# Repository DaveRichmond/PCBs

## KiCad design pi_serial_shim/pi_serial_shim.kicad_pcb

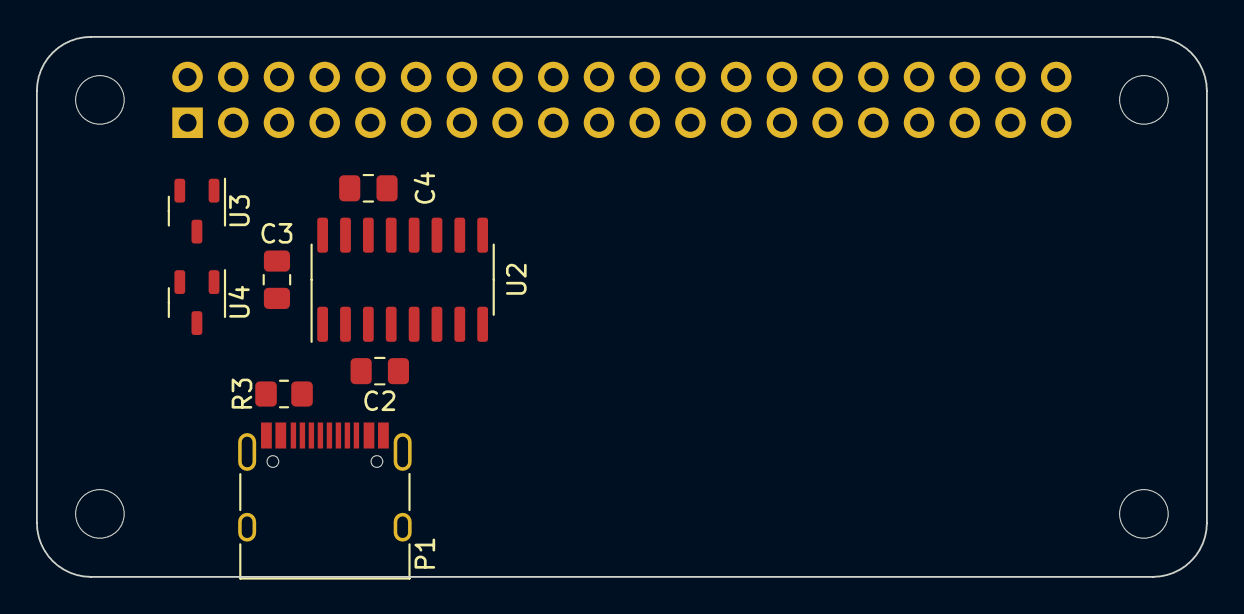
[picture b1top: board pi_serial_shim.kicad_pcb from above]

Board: 2 copper layers, 65.0 x 30.0 mm, 13 parts (1 on the bottom side), 10 nets, no tracks yet.

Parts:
C2: 100n; C_0805_2012Metric_Pad1.18x1.45mm_HandSolder
C3, C4: 1u; C_0805_2012Metric_Pad1.18x1.45mm_HandSolder
J1: GPIO; PinSocket_2x20_P2.54mm_Vertical
MH1, MH2, MH3, MH4: MountingHole_2.7mm_M2.5
P1: USB_C_Plug_USB2.0; USB_C_Receptacle_HRO_TYPE-C-31-M-12
R3: 56k; R_0805_2012Metric_Pad1.20x1.40mm_HandSolder
U2: SOIC-16_3.9x9.9mm_P1.27mm
U3, U4: SOT-23-3

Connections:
+3.3V: C4.1, J1.1, J1.17, U2.15 (VIO), U3.2 (VO)
+5V: C3.1, J1.2, J1.4, U2.16 (VCC), U4.2 (VO)
/GPIO14/TXD0: J1.8, U2.3 (RXD)
/GPIO15/RXD0: J1.10, U2.2 (TXD)
GND: C2.2, C3.2, C4.2, J1.6, J1.9, J1.14, J1.20, J1.25, J1.30, J1.34, J1.39, P1.A1 (GND), P1.A12 (GND), P1.B1 (GND), P1.B12 (GND), P1.S1 (SHIELD), U2.1 (GND), U3.1 (GND), U4.1 (GND)
unnamed: P1.A5 (CC), R3.2
unnamed: P1.A6 (D+), U2.5 (UD+)
unnamed: P1.A7 (D-), U2.6 (UD-)
unnamed: P1.A4 (VBUS), P1.A9 (VBUS), P1.B4 (VBUS), P1.B5 (VCONN), P1.B9 (VBUS), R3.1, U4.3 (VI)
unnamed: C2.1, U2.4 (V3), U3.3 (VI)

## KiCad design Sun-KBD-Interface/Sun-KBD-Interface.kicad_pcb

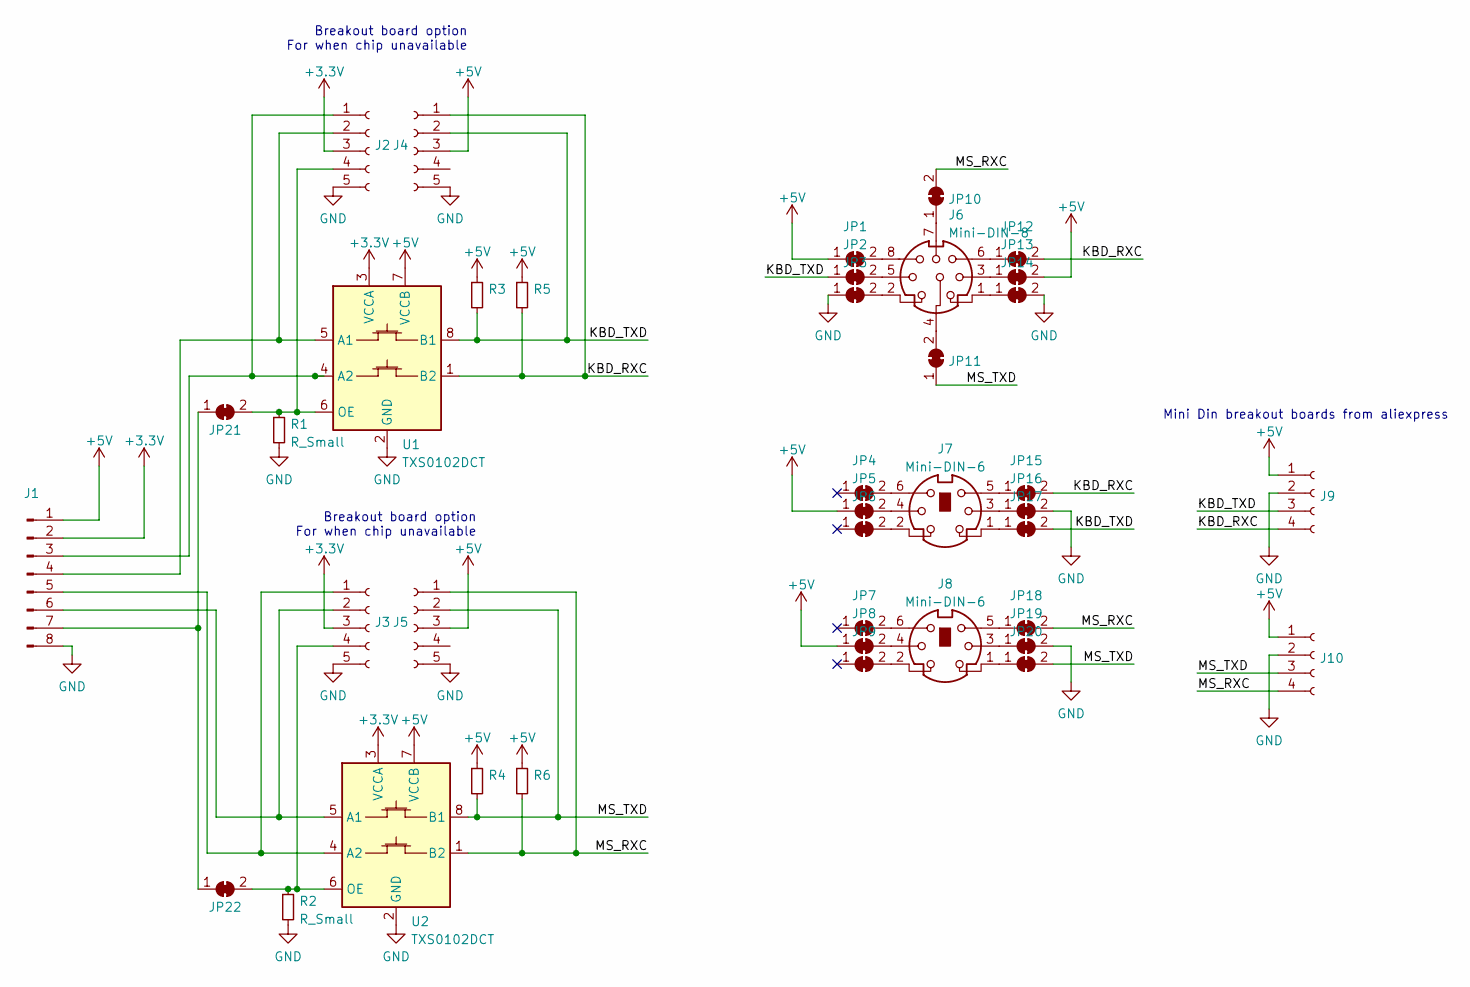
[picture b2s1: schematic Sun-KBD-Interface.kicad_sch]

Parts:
J1: Conn_01x08_Male; PinHeader_1x08_P2.54mm_Vertical
J2, J3, J4, J5: Conn_01x05_Female; PinHeader_1x05_P2.54mm_Vertical
J6: Mini-DIN-8; Mini-DIN 8
J7, J8: Mini-DIN-6; Mini-DIN 6
J9, J10: Conn_01x04_Female; PinSocket_1x04_P2.54mm_Vertical
JP1, JP2, JP3, JP4, JP5, JP6, JP7, JP8, JP9, JP10, JP11, JP12, JP13, JP14, JP15, JP16, JP17, JP18, JP19, JP20, JP21, JP22: SolderJumper_2_Bridged; SolderJumper-2_P1.3mm_Bridged_RoundedPad1.0x1.5mm
R1, R2, R3, R4, R5, R6: R_Small; R_1206_3216Metric_Pad1.30x1.75mm_HandSolder
U1, U2: TXS0102DCT; SSOP-8_2.95x2.8mm_P0.65mm

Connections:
+3.3V: J1.2, J2.3, J3.3, U1.3 (VCCA), U2.3 (VCCA)
+5V: J1.1, J4.3, J5.3, J9.1, J10.1, JP1.1 (A), JP5.1 (A), JP8.1 (A), JP13.2 (B), R3.1, R4.1, R5.1, R6.1, U1.7 (VCCB), U2.7 (VCCB)
/KBD_RXC: J4.1, J9.4, JP12.2 (B), JP15.2 (B), R5.2, U1.1 (B2)
/KBD_TXD: J4.2, J9.3, JP2.1 (A), JP17.2 (B), R3.2, U1.8 (B1)
/MS_RXC: J5.1, J10.4, JP10.2 (B), JP18.2 (B), R6.2, U2.1 (B2)
/MS_TXD: J5.2, J10.3, JP11.1 (A), JP20.2 (B), R4.2, U2.8 (B1)
GND: J1.8, J2.5, J3.5, J4.5, J5.5, J9.2, J10.2, JP3.1 (A), JP14.2 (B), JP16.2 (B), JP19.2 (B), R1.2, R2.2, U1.2 (GND), U2.2 (GND)
unnamed: J1.3, J2.1, U1.4 (A2)
unnamed: J1.4, J2.2, U1.5 (A1)
unnamed: J1.5, J3.1, U2.4 (A2)
unnamed: J1.6, J3.2, U2.5 (A1)
unnamed: J1.7, JP21.1 (A), JP22.1 (A)
unnamed: J2.4, JP21.2 (B), R1.1, U1.6 (OE)
unnamed: J3.4, JP22.2 (B), R2.1, U2.6 (OE)
unnamed: J6.1, JP14.1 (A)
unnamed: J6.2, JP3.2 (B)
unnamed: J6.3, JP13.1 (A)
unnamed: J6.4, JP11.2 (B)
unnamed: J6.5, JP2.2 (B)
unnamed: J6.6, JP12.1 (A)
unnamed: J6.7, JP10.1 (A)
unnamed: J6.8, JP1.2 (B)
unnamed: J7.1, JP17.1 (A)
unnamed: J7.2, JP6.2 (B)
unnamed: J7.3, JP16.1 (A)
unnamed: J7.4, JP5.2 (B)
unnamed: J7.5, JP15.1 (A)
unnamed: J7.6, JP4.2 (B)
unnamed: J8.1, JP20.1 (A)
unnamed: J8.2, JP9.2 (B)
unnamed: J8.3, JP19.1 (A)
unnamed: J8.4, JP8.2 (B)
unnamed: J8.5, JP18.1 (A)
unnamed: J8.6, JP7.2 (B)

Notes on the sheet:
Breakout board option For when chip unavailable
Mini Din breakout boards from aliexpress

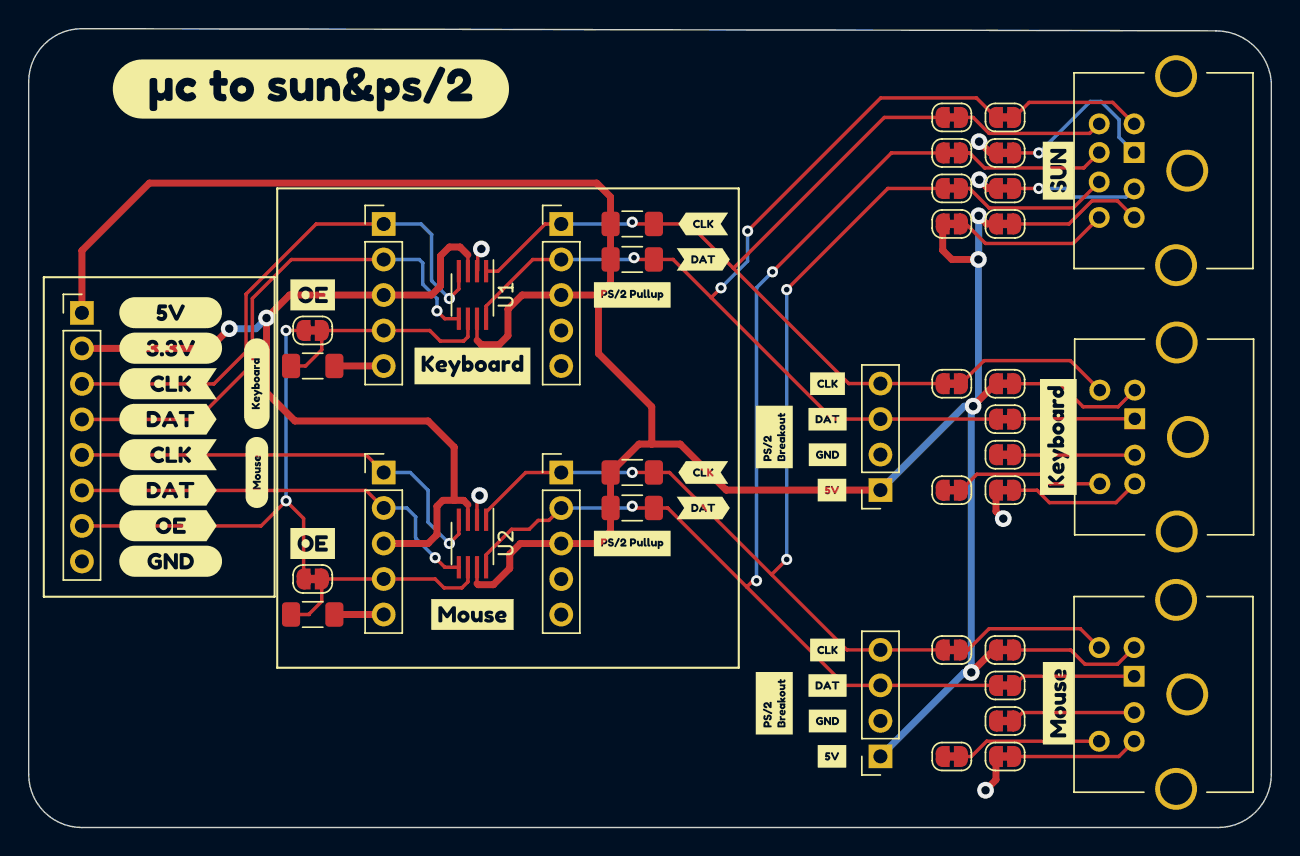
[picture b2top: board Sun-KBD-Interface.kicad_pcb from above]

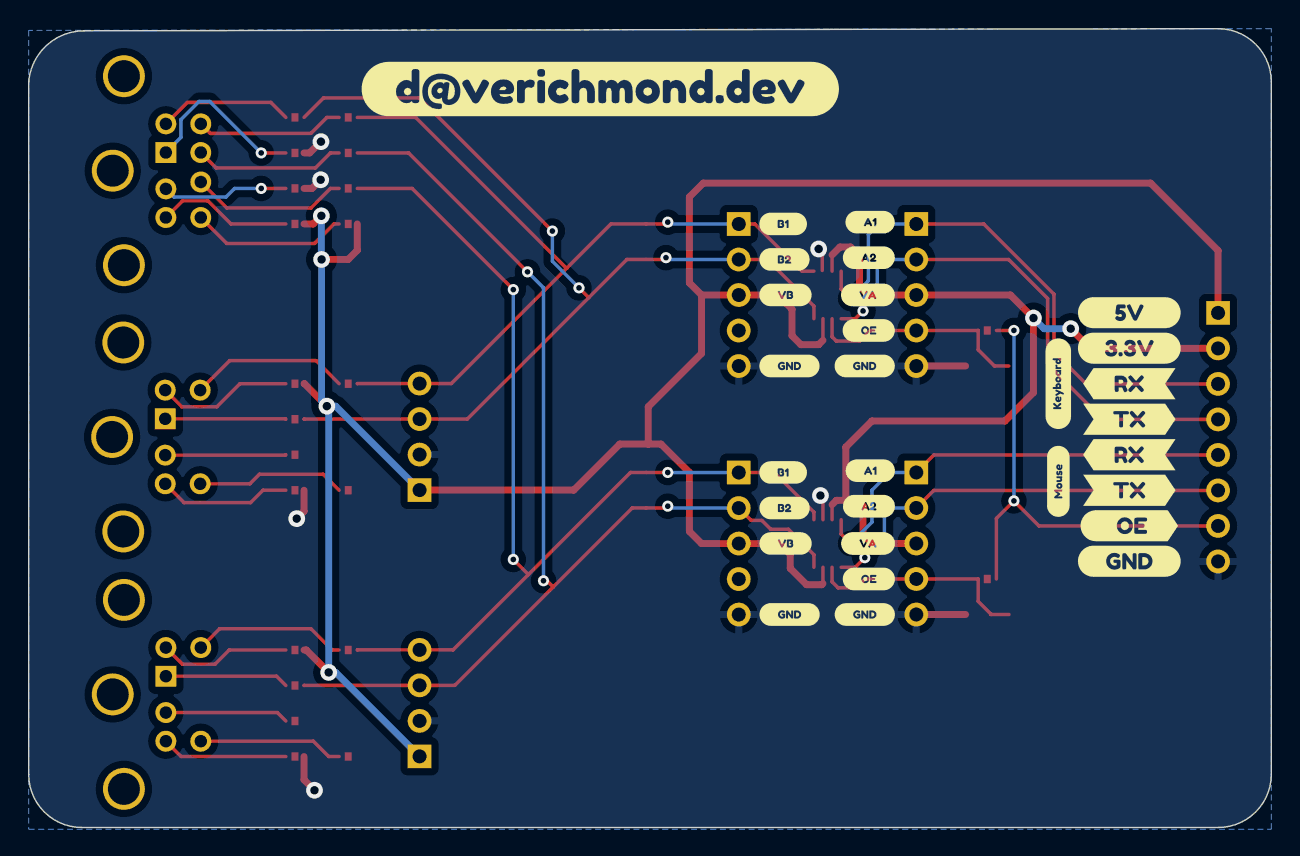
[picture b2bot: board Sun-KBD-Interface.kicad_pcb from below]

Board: 2 copper layers, 88.9 x 57.1 mm, 103 parts (29 on the bottom side), 34 nets.

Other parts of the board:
kibuzzard-1: G***; kibuzzard-6300B3A5
kibuzzard-2: G***; kibuzzard-6300B393
kibuzzard-3, kibuzzard-32: G***; kibuzzard-6300B04A
kibuzzard-4, kibuzzard-17: G***; kibuzzard-6300AFFB
kibuzzard-5, kibuzzard-19: G***; kibuzzard-6300B08C
kibuzzard-6, kibuzzard-21: G***; kibuzzard-6300B0E5
kibuzzard-7, kibuzzard-20: G***; kibuzzard-6300B0D2
kibuzzard-8: G***; kibuzzard-6300B1CF
kibuzzard-9, kibuzzard-9#2: G***; kibuzzard-6300B31A
kibuzzard-10, kibuzzard-12: G***; kibuzzard-6300B379
kibuzzard-11, kibuzzard-14: G***; kibuzzard-6300B34C
kibuzzard-13, kibuzzard-13#2: G***; kibuzzard-6300B361
kibuzzard-15, kibuzzard-15#2: G***; kibuzzard-6300B3DE
kibuzzard-16, kibuzzard-31: G***; kibuzzard-6300B05D
kibuzzard-18, kibuzzard-18#2: G***; kibuzzard-6300B3ED
kibuzzard-22, kibuzzard-23: G***; kibuzzard-6300B12D
kibuzzard-24, kibuzzard-29: G***; kibuzzard-6300B164
kibuzzard-25, kibuzzard-27: G***; kibuzzard-6300B180
kibuzzard-26, kibuzzard-28: G***; kibuzzard-6300B189
kibuzzard-30, kibuzzard-33: G***; kibuzzard-6300B14F
kibuzzard-63B4EFA4: G***; kibuzzard-63B4EFA4
kibuzzard-63B4EFB4: G***; kibuzzard-63B4EFB4
kibuzzard-63B4F027, kibuzzard-63B4F027#2: G***; kibuzzard-63B4F027
kibuzzard-63B4F037, kibuzzard-63B4F037#2: G***; kibuzzard-63B4F037
kibuzzard-63043A3B, kibuzzard-63043A3B#2: G***; kibuzzard-63043A3B
kibuzzard-63043A22, kibuzzard-63043A22#2: G***; kibuzzard-63043A22
kibuzzard-63043A32, kibuzzard-63043A32#2: G***; kibuzzard-63043A32
kibuzzard-63043B6D: G***; kibuzzard-63043B6D
kibuzzard-63043B8B: G***; kibuzzard-63043B8B
kibuzzard-630439AA, kibuzzard-630439AA#2: G***; kibuzzard-630439AA
kibuzzard-630439CC, kibuzzard-630439CC#2: G***; kibuzzard-630439CC
kibuzzard-630439D9, kibuzzard-630439D9#2: G***; kibuzzard-630439D9
kibuzzard-630439E7, kibuzzard-630439E7#2: G***; kibuzzard-630439E7
kibuzzard-630439F1, kibuzzard-630439F1#2, kibuzzard-630439F1#3, kibuzzard-630439F1#4: G***; kibuzzard-630439F1

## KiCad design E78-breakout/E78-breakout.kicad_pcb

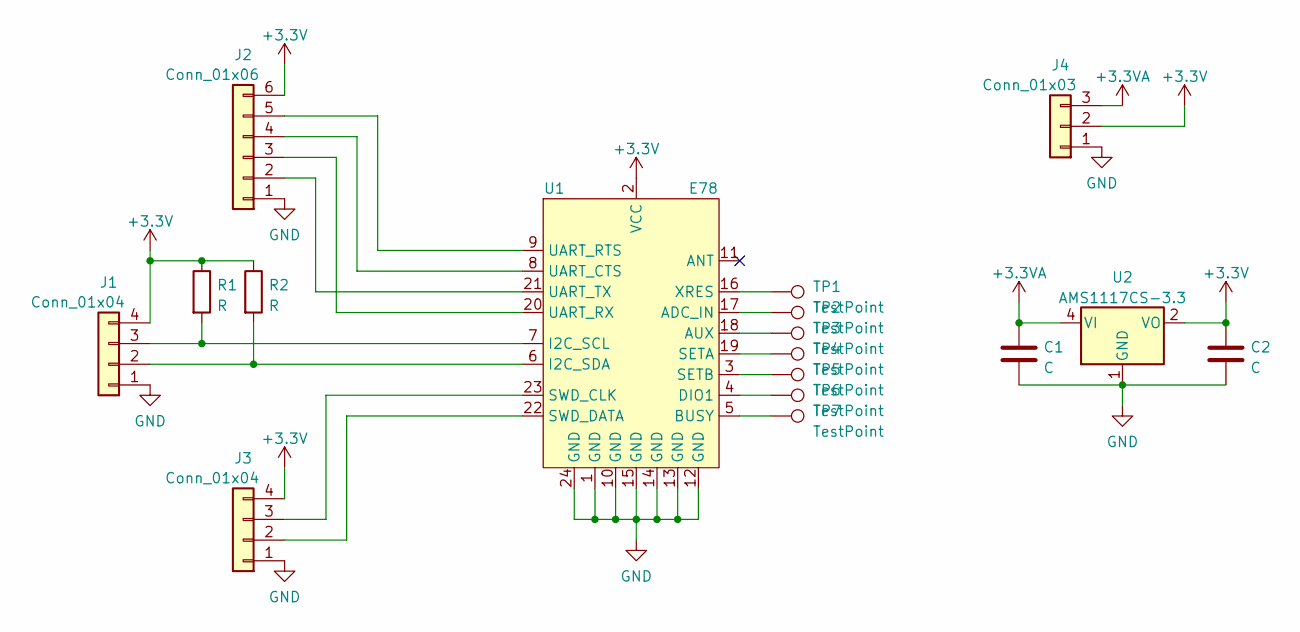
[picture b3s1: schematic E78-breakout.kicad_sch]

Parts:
C1, C2: C; C_0805_2012Metric_Pad1.18x1.45mm_HandSolder
J1, J3: Conn_01x04; PinSocket_1x04_P2.54mm_Vertical
J2: Conn_01x06; PinSocket_1x06_P2.54mm_Vertical
J4: Conn_01x03; PinSocket_1x03_P2.54mm_Vertical
R1, R2: R; R_0805_2012Metric_Pad1.20x1.40mm_HandSolder
TP1, TP2, TP3, TP4, TP5, TP6, TP7: TestPoint; TestPoint_Pad_D1.5mm
U1: E78; ebyte e78
U2: AMS1117CS-3.3; SOIC-8_3.9x4.9mm_P1.27mm

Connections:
+3.3VA: C1.1, J4.3, U2.4 (VI)
+3V3: C2.1, J1.4, J2.6, J3.4, J4.2, R1.1, R2.1, U1.2 (VCC), U2.2 (VO), U2.3 (VO), U2.6 (VO), U2.7 (VO)
GND: C1.2, C2.2, J1.1, J2.1, J3.1, J4.1, U1.1 (GND), U1.10 (GND), U1.12 (GND), U1.13 (GND), U1.14 (GND), U1.15 (GND), U1.24 (GND), U2.1 (GND)
unnamed: J1.2, R2.2, U1.6 (I2C_SDA)
unnamed: J1.3, R1.2, U1.7 (I2C_SCL)
unnamed: J2.2, U1.21 (UART_TX)
unnamed: J2.3, U1.20 (UART_RX)
unnamed: J2.4, U1.8 (UART_CTS)
unnamed: J2.5, U1.9 (UART_RTS)
unnamed: J3.2, U1.22 (SWD_DATA)
unnamed: J3.3, U1.23 (SWD_CLK)
unnamed: TP2.1, U1.17 (ADC_IN)
unnamed: TP3.1, U1.18 (AUX)
unnamed: TP7.1, U1.5 (BUSY)
unnamed: TP6.1, U1.4 (DIO1)
unnamed: TP4.1, U1.19 (SETA)
unnamed: TP5.1, U1.3 (SETB)
unnamed: TP1.1, U1.16 (XRES)

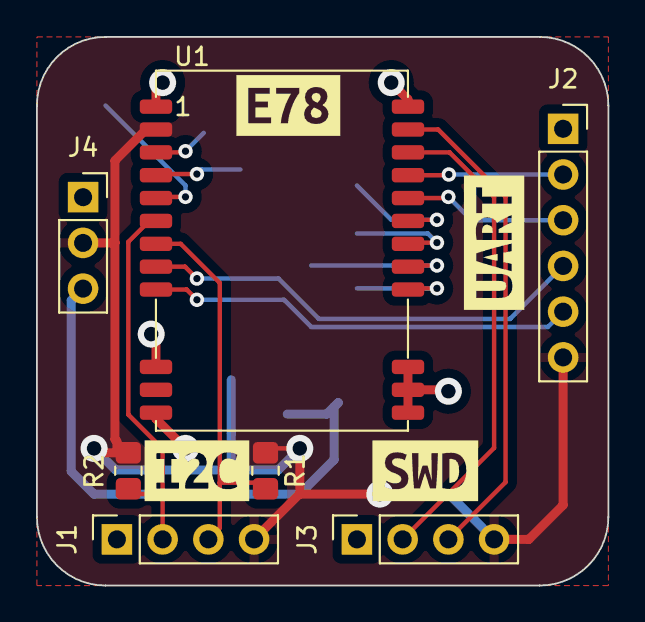
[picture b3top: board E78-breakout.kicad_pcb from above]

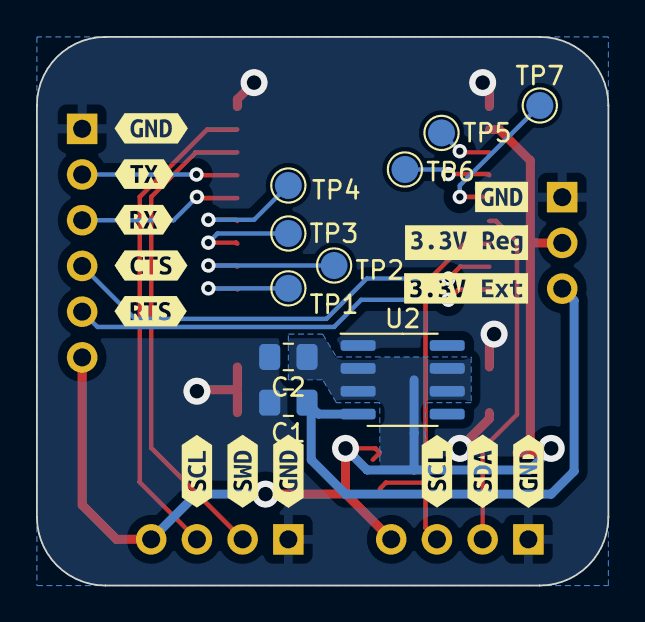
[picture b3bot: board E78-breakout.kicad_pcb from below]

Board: 2 copper layers, 31.8 x 30.5 mm, 35 parts (24 on the bottom side), 18 nets.

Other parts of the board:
kibuzzard-64A3B5A1: G***; kibuzzard-64A3B5A1
kibuzzard-64A3B5B5: G***; kibuzzard-64A3B5B5
kibuzzard-64A3B5D3: G***; kibuzzard-64A3B5D3
kibuzzard-64A3B52E: G***; kibuzzard-64A3B52E
kibuzzard-64A3B61D: G***; kibuzzard-64A3B61D
kibuzzard-64A3B63B: G***; kibuzzard-64A3B63B
kibuzzard-64A3B516: G***; kibuzzard-64A3B516
kibuzzard-64A3B571: G***; kibuzzard-64A3B571
kibuzzard-64A3B602: G***; kibuzzard-64A3B602
kibuzzard-64A3B618: G***; kibuzzard-64A3B618
kibuzzard-64A3B637: G***; kibuzzard-64A3B637
kibuzzard-6402D7DF: G***; kibuzzard-6402D7DF
kibuzzard-6402D81D: G***; kibuzzard-6402D81D
kibuzzard-6402D83E: G***; kibuzzard-6402D83E
kibuzzard-6402D86B: G***; kibuzzard-6402D86B
kibuzzard-6402D830: G***; kibuzzard-6402D830
kibuzzard-6402D864: G***; kibuzzard-6402D864
kibuzzard-6402EA7B: G***; kibuzzard-6402EA7B

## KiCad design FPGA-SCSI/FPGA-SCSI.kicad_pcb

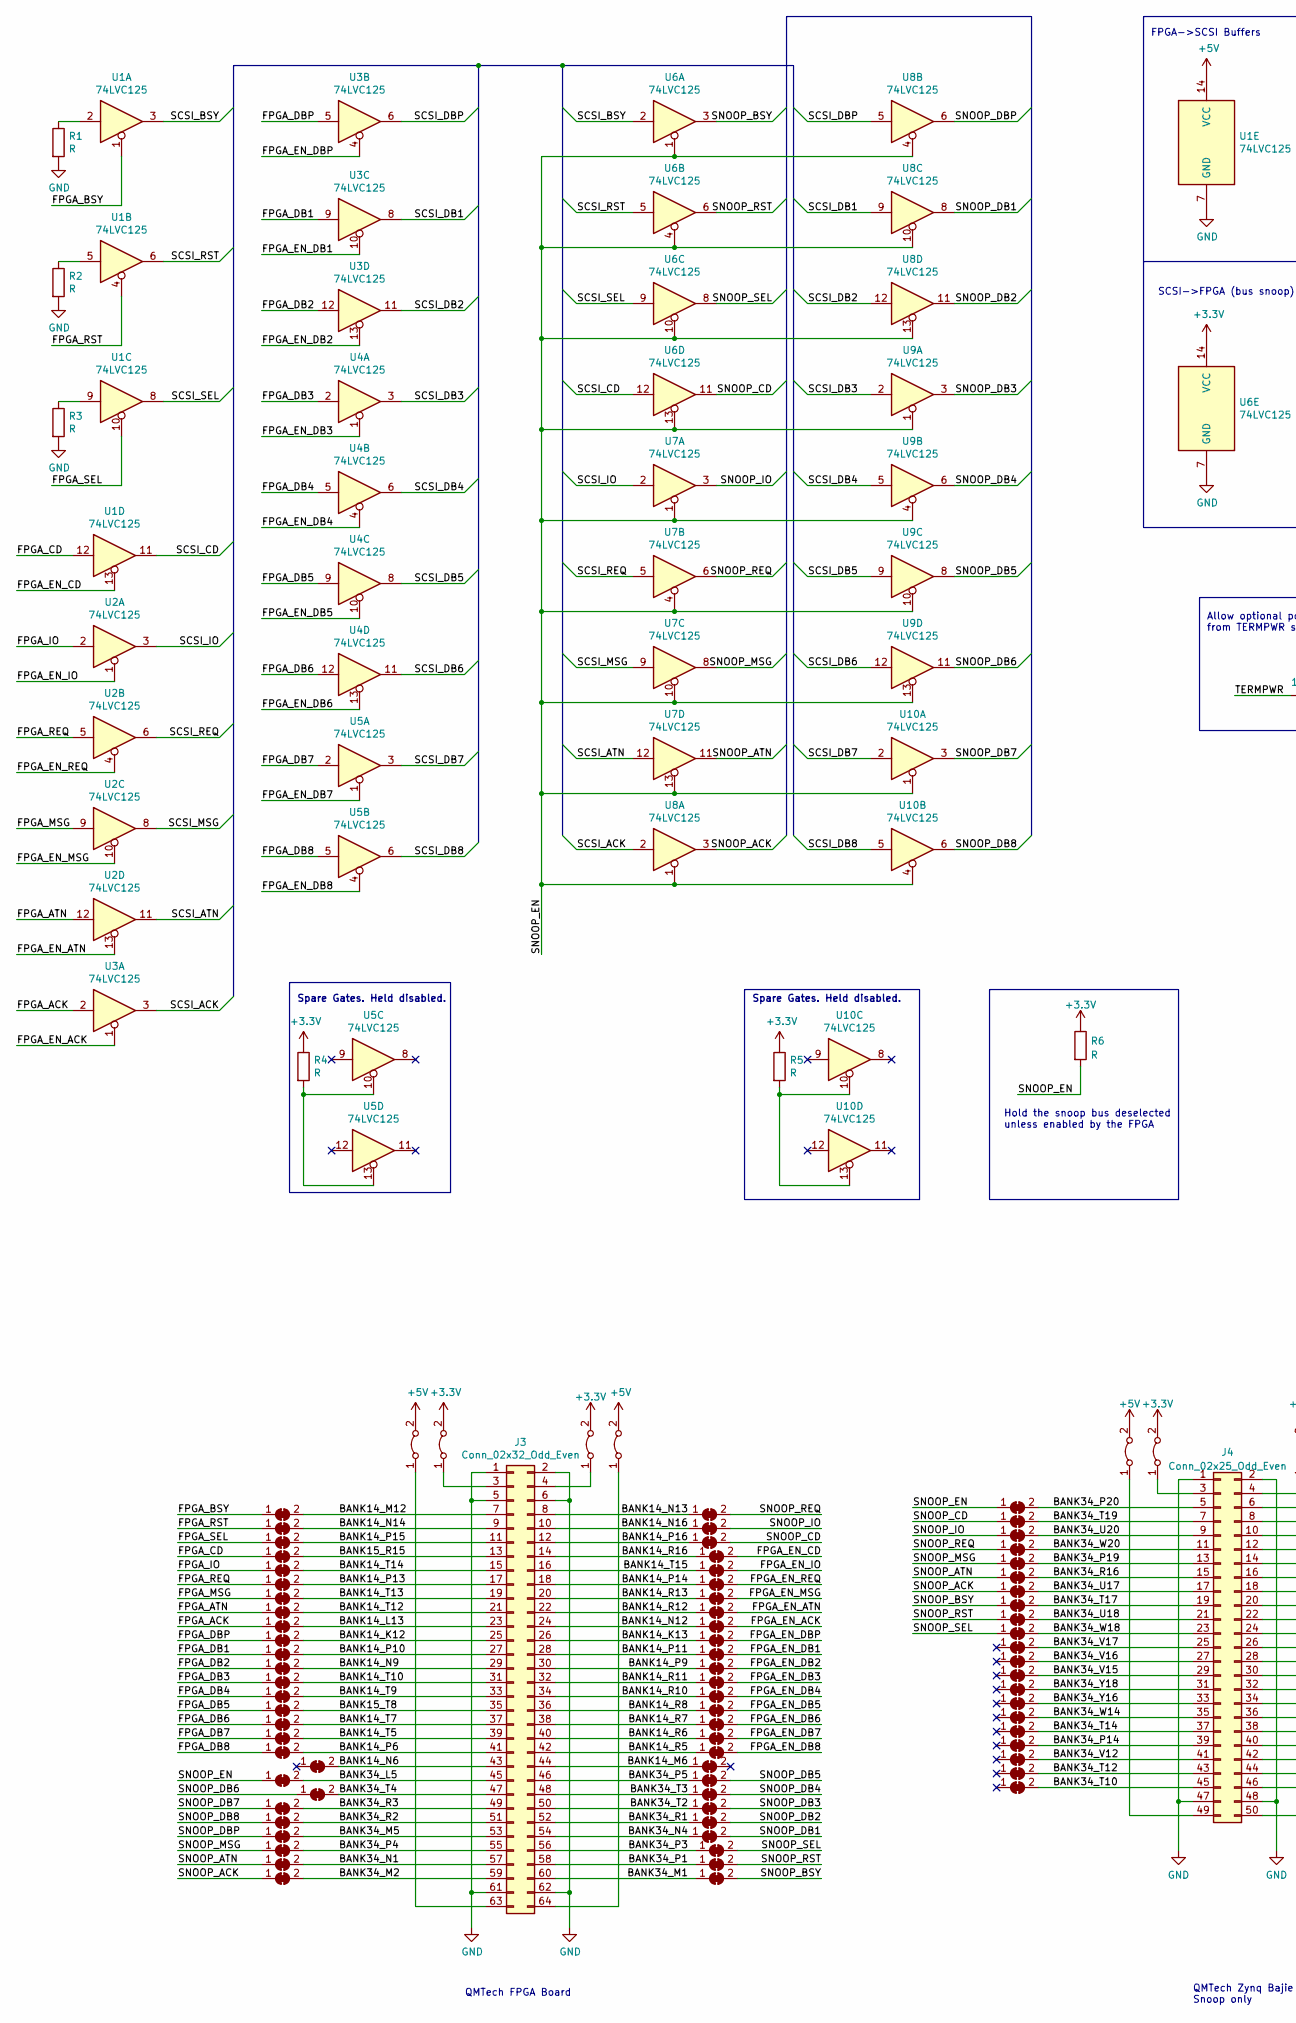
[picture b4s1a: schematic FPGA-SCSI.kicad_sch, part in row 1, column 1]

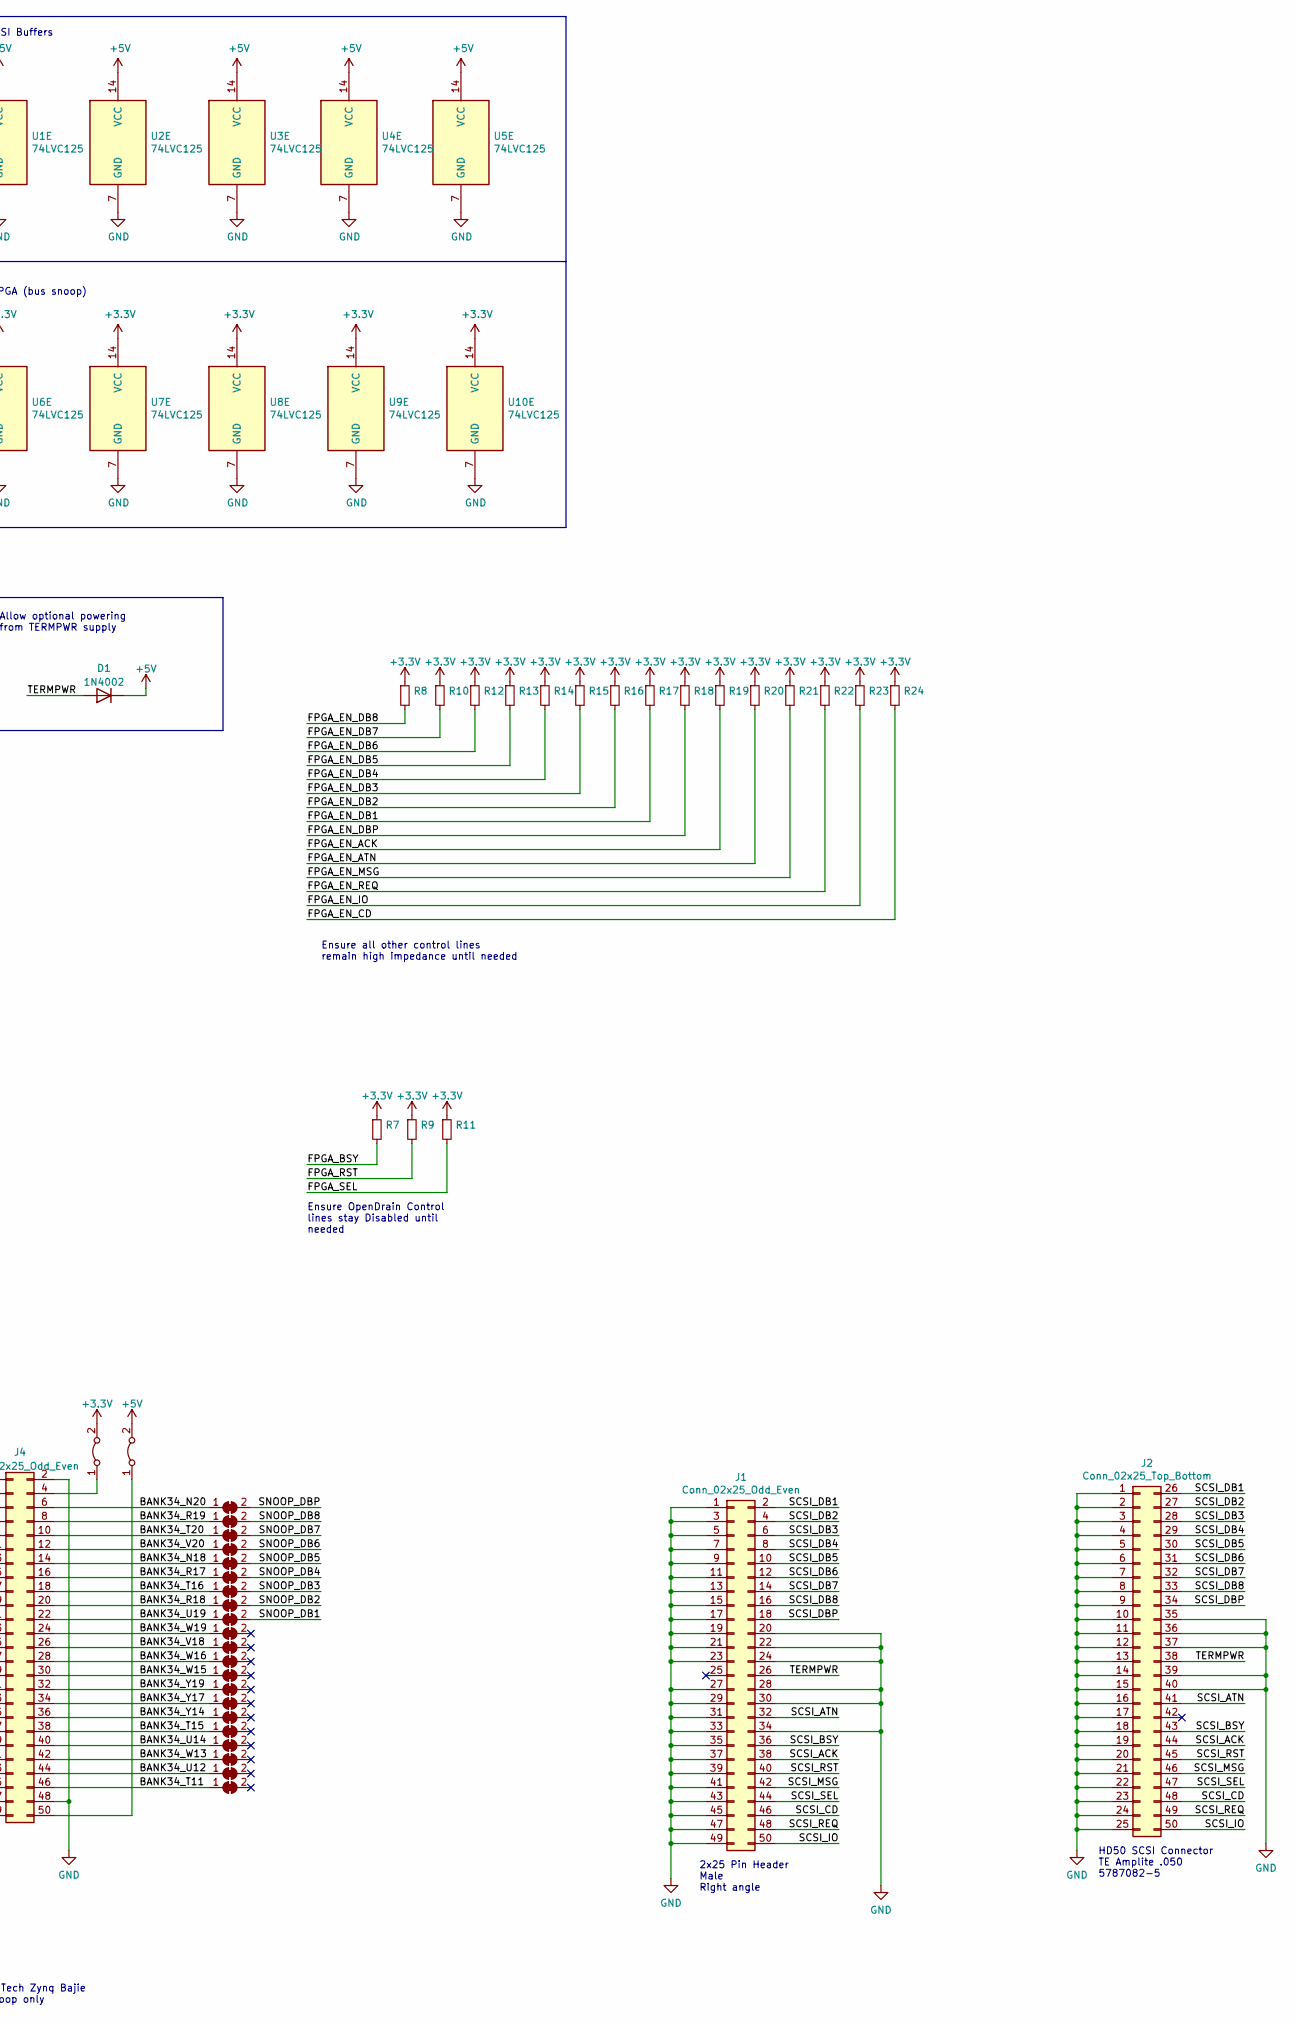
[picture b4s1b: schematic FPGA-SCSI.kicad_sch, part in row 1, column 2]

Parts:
D1: 1N4002; D_DO-41_SOD81_P10.16mm_Horizontal
J1, J4: Conn_02x25_Odd_Even; PinHeader_2x25_P2.54mm_Vertical
J2: Conn_02x25_Top_Bottom; Amplite .050 2x25
J3: Conn_02x32_Odd_Even; PinSocket_2x32_P2.54mm_Vertical
JP1, JP2, JP3, JP4, JP5, JP6, JP7, JP8, JP9, JP10, JP11, JP12, JP13, JP14, JP15, JP16, JP17, JP18, JP19, JP20, JP21, JP22, JP23, JP24, JP25, JP29, JP30, JP31, JP32, JP33, JP34, JP35, JP36, JP37, JP38, JP39, JP40, JP41, JP42, JP43, JP44, JP45, JP46, JP48, JP49, JP50, JP51, JP52, JP53, JP54, JP55, JP56, JP57, JP58, JP59, JP60, JP61, JP62, JP63, JP64, JP65, JP70, JP71, JP72, JP73, JP74, JP75, JP76, JP77, JP78, JP79, JP80, JP81, JP82, JP83, JP84, JP85, JP86, JP87, JP88, JP89, JP90, JP91, JP92, JP93, JP94, JP95, JP96, JP97, JP98, JP99, JP100, JP101, JP102, JP103, JP104: Jumper_NC_Small; SolderJumper-2_P1.3mm_Bridged_RoundedPad1.0x1.5mm
JP26, JP27, JP28, JP47, JP66, JP67, JP68, JP69: Jumper_2_Bridged; SolderJumper-2_P1.3mm_Bridged_RoundedPad1.0x1.5mm
R1, R2, R3, R4, R5, R6: R; R_0805_2012Metric_Pad1.20x1.40mm_HandSolder
R7, R8, R9, R10, R11, R12, R13, R14, R15, R16, R17, R18, R19, R20, R21, R22, R23, R24: R_Small; R_0805_2012Metric_Pad1.20x1.40mm_HandSolder
U1, U2, U3, U4, U5, U6, U7, U8, U9, U10: 74LVC125; SOIC-14_3.9x8.7mm_P1.27mm

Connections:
+5V: D1.1 (K), JP26.2 (B), JP47.2 (B), JP66.2 (B), JP69.2 (B), U1.14 (VCC), U2.14 (VCC), U3.14 (VCC), U4.14 (VCC), U5.14 (VCC)
/BANK14_K12: J3.25, JP10.2 (B)
/BANK14_K13: J3.26, JP35.1 (A)
/BANK14_L13: J3.23, JP9.2 (B)
/BANK14_M6: J3.44, JP63.1 (A)
/BANK14_M12: J3.7, JP1.2 (B)
/BANK14_N6: J3.43, JP58.2 (B)
/BANK14_N9: J3.29, JP12.2 (B)
/BANK14_N12: J3.24, JP34.1 (A)
/BANK14_N13: J3.8, JP60.1 (A)
/BANK14_N14: J3.9, JP2.2 (B)
/BANK14_N16: J3.10, JP61.1 (A)
/BANK14_P6: J3.41, JP18.2 (B)
/BANK14_P9: J3.30, JP37.1 (A)
/BANK14_P10: J3.27, JP11.2 (B)
/BANK14_P11: J3.28, JP36.1 (A)
/BANK14_P13: J3.17, JP6.2 (B)
/BANK14_P14: J3.18, JP31.1 (A)
/BANK14_P15: J3.11, JP3.2 (B)
/BANK14_P16: J3.12, JP62.1 (A)
/BANK14_R5: J3.42, JP43.1 (A)
/BANK14_R6: J3.40, JP42.1 (A)
/BANK14_R7: J3.38, JP41.1 (A)
/BANK14_R8: J3.36, JP40.1 (A)
/BANK14_R10: J3.34, JP39.1 (A)
/BANK14_R11: J3.32, JP38.1 (A)
/BANK14_R12: J3.22, JP33.1 (A)
/BANK14_R13: J3.20, JP32.1 (A)
/BANK14_R16: J3.14, JP29.1 (A)
/BANK14_T5: J3.39, JP17.2 (B)
/BANK14_T7: J3.37, JP16.2 (B)
/BANK14_T9: J3.33, JP14.2 (B)
/BANK14_T10: J3.31, JP13.2 (B)
/BANK14_T12: J3.21, JP8.2 (B)
/BANK14_T13: J3.19, JP7.2 (B)
/BANK14_T14: J3.15, JP5.2 (B)
/BANK14_T15: J3.16, JP30.1 (A)
/BANK15_R15: J3.13, JP4.2 (B)
/BANK15_T8: J3.35, JP15.2 (B)
/BANK34_L5: J3.45, JP19.2 (B)
/BANK34_M1: J3.60, JP46.1 (A)
/BANK34_M2: J3.59, JP25.2 (B)
/BANK34_M5: J3.53, JP22.2 (B)
/BANK34_N1: J3.57, JP24.2 (B)
/BANK34_N4: J3.54, JP81.1 (A)
/BANK34_N18: J4.14, JP74.1 (A)
/BANK34_N20: J4.6, JP70.1 (A)
/BANK34_P1: J3.58, JP45.1 (A)
/BANK34_P3: J3.56, JP44.1 (A)
/BANK34_P4: J3.55, JP23.2 (B)
/BANK34_P5: J3.46, JP64.1 (A)
/BANK34_P14: J4.39, JP89.2 (B)
/BANK34_P19: J4.13, JP52.2 (B)
/BANK34_P20: J4.5, JP48.2 (B)
/BANK34_R1: J3.52, JP80.1 (A)
/BANK34_R2: J3.51, JP21.2 (B)
/BANK34_R3: J3.49, JP20.2 (B)
/BANK34_R16: J4.15, JP53.2 (B)
/BANK34_R17: J4.16, JP75.1 (A)
/BANK34_R18: J4.20, JP77.1 (A)
/BANK34_R19: J4.8, JP71.1 (A)
/BANK34_T2: J3.50, JP79.1 (A)
/BANK34_T3: J3.48, JP65.1 (A)
/BANK34_T4: J3.47, JP59.2 (B)
/BANK34_T10: J4.45, JP92.2 (B)
/BANK34_T11: J4.46, JP104.1 (A)
/BANK34_T12: J4.43, JP91.2 (B)
/BANK34_T14: J4.37, JP88.2 (B)
/BANK34_T15: J4.38, JP100.1 (A)
/BANK34_T16: J4.18, JP76.1 (A)
/BANK34_T17: J4.19, JP55.2 (B)
/BANK34_T19: J4.7, JP49.2 (B)
/BANK34_T20: J4.10, JP72.1 (A)
/BANK34_U12: J4.44, JP103.1 (A)
/BANK34_U14: J4.40, JP101.1 (A)
/BANK34_U17: J4.17, JP54.2 (B)
/BANK34_U18: J4.21, JP56.2 (B)
/BANK34_U19: J4.22, JP78.1 (A)
/BANK34_U20: J4.9, JP50.2 (B)
/BANK34_V12: J4.41, JP90.2 (B)
/BANK34_V15: J4.29, JP84.2 (B)
/BANK34_V16: J4.27, JP83.2 (B)
/BANK34_V17: J4.25, JP82.2 (B)
/BANK34_V18: J4.26, JP94.1 (A)
/BANK34_V20: J4.12, JP73.1 (A)
/BANK34_W13: J4.42, JP102.1 (A)
/BANK34_W14: J4.35, JP87.2 (B)
/BANK34_W15: J4.30, JP96.1 (A)
/BANK34_W16: J4.28, JP95.1 (A)
/BANK34_W18: J4.23, JP57.2 (B)
/BANK34_W19: J4.24, JP93.1 (A)
/BANK34_W20: J4.11, JP51.2 (B)
/BANK34_Y14: J4.36, JP99.1 (A)
/BANK34_Y16: J4.33, JP86.2 (B)
/BANK34_Y17: J4.34, JP98.1 (A)
/BANK34_Y18: J4.31, JP85.2 (B)
/BANK34_Y19: J4.32, JP97.1 (A)
/FPGA_ACK: JP9.1 (A), U3.2
/FPGA_ATN: JP8.1 (A), U2.12
/FPGA_BSY: JP1.1 (A), R7.2, U1.1
/FPGA_CD: JP4.1 (A), U1.12
/FPGA_DB1: JP11.1 (A), U3.9
/FPGA_DB2: JP12.1 (A), U3.12
/FPGA_DB3: JP13.1 (A), U4.2
/FPGA_DB4: JP14.1 (A), U4.5
/FPGA_DB5: JP15.1 (A), U4.9
/FPGA_DB6: JP16.1 (A), U4.12
/FPGA_DB7: JP17.1 (A), U5.2
/FPGA_DB8: JP18.1 (A), U5.5
/FPGA_DBP: JP10.1 (A), U3.5
/FPGA_EN_ACK: JP34.2 (B), R19.2, U3.1
/FPGA_EN_ATN: JP33.2 (B), R20.2, U2.13
/FPGA_EN_CD: JP29.2 (B), R24.2, U1.13
/FPGA_EN_DB1: JP36.2 (B), R17.2, U3.10
/FPGA_EN_DB2: JP37.2 (B), R16.2, U3.13
/FPGA_EN_DB3: JP38.2 (B), R15.2, U4.1
/FPGA_EN_DB4: JP39.2 (B), R14.2, U4.4
/FPGA_EN_DB5: JP40.2 (B), R13.2, U4.10
/FPGA_EN_DB6: JP41.2 (B), R12.2, U4.13
/FPGA_EN_DB7: JP42.2 (B), R10.2, U5.1
/FPGA_EN_DB8: JP43.2 (B), R8.2, U5.4
/FPGA_EN_DBP: JP35.2 (B), R18.2, U3.4
/FPGA_EN_IO: JP30.2 (B), R23.2, U2.1
/FPGA_EN_MSG: JP32.2 (B), R21.2, U2.10
/FPGA_EN_REQ: JP31.2 (B), R22.2, U2.4
/FPGA_IO: JP5.1 (A), U2.2
/FPGA_MSG: JP7.1 (A), U2.9
/FPGA_REQ: JP6.1 (A), U2.5
/FPGA_RST: JP2.1 (A), R9.2, U1.4
/FPGA_SEL: JP3.1 (A), R11.2, U1.10
/SCSI_ACK: J1.38, J2.44, U3.3, U8.2
/SCSI_ATN: J1.32, J2.41, U2.11, U7.12
/SCSI_BSY: J1.36, J2.43, U1.3, U6.2
/SCSI_CD: J1.46, J2.48, U1.11, U6.12
/SCSI_DB1: J1.2, J2.26, U3.8, U8.9
/SCSI_DB2: J1.4, J2.27, U3.11, U8.12
/SCSI_DB3: J1.6, J2.28, U4.3, U9.2
/SCSI_DB4: J1.8, J2.29, U4.6, U9.5
/SCSI_DB5: J1.10, J2.30, U4.8, U9.9
/SCSI_DB6: J1.12, J2.31, U4.11, U9.12
/SCSI_DB7: J1.14, J2.32, U5.3, U10.2
/SCSI_DB8: J1.16, J2.33, U5.6, U10.5
/SCSI_DBP: J1.18, J2.34, U3.6, U8.5
/SCSI_IO: J1.50, J2.50, U2.3, U7.2
/SCSI_MSG: J1.42, J2.46, U2.8, U7.9
/SCSI_REQ: J1.48, J2.49, U2.6, U7.5
/SCSI_RST: J1.40, J2.45, U1.6, U6.5
/SCSI_SEL: J1.44, J2.47, U1.8, U6.9
/SNOOP_ACK: JP25.1 (A), JP54.1 (A), U8.3
/SNOOP_ATN: JP24.1 (A), JP53.1 (A), U7.11
/SNOOP_BSY: JP46.2 (B), JP55.1 (A), U6.3
/SNOOP_CD: JP49.1 (A), JP62.2 (B), U6.11
/SNOOP_DB1: JP78.2 (B), JP81.2 (B), U8.8
/SNOOP_DB2: JP77.2 (B), JP80.2 (B), U8.11
/SNOOP_DB3: JP76.2 (B), JP79.2 (B), U9.3
/SNOOP_DB4: JP65.2 (B), JP75.2 (B), U9.6
/SNOOP_DB5: JP64.2 (B), JP74.2 (B), U9.8
/SNOOP_DB6: JP59.1 (A), JP73.2 (B), U9.11
/SNOOP_DB7: JP20.1 (A), JP72.2 (B), U10.3
/SNOOP_DB8: JP21.1 (A), JP71.2 (B), U10.6
/SNOOP_DBP: JP22.1 (A), JP70.2 (B), U8.6
/SNOOP_EN: JP19.1 (A), JP48.1 (A), R6.2, U6.1, U6.4, U6.10, U6.13, U7.1, U7.4, U7.10, U7.13, U8.1, U8.4, U8.10, U8.13, U9.1, U9.4, U9.10, U9.13, U10.1, U10.4
/SNOOP_IO: JP50.1 (A), JP61.2 (B), U7.3
/SNOOP_MSG: JP23.1 (A), JP52.1 (A), U7.8
/SNOOP_REQ: JP51.1 (A), JP60.2 (B), U7.6
/SNOOP_RST: JP45.2 (B), JP56.1 (A), U6.6
/SNOOP_SEL: JP44.2 (B), JP57.1 (A), U6.8
/TERMPWR: D1.2 (A), J1.26, J2.38
GND: J1.1, J1.3, J1.5, J1.7, J1.9, J1.11, J1.13, J1.15, J1.17, J1.19, J1.20, J1.21, J1.22, J1.23, J1.24, J1.27, J1.28, J1.29, J1.30, J1.31, J1.33, J1.34, J1.35, J1.37, J1.39, J1.41, J1.43, J1.45, J1.47, J1.49, J2.1, J2.2, J2.3, J2.4, J2.5, J2.6, J2.7, J2.8, J2.9, J2.10, J2.11, J2.12, J2.13, J2.14, J2.15, J2.16, J2.17, J2.18, J2.19, J2.20, J2.21, J2.22, J2.23, J2.24, J2.25, J2.35, J2.36, J2.37, J2.39, J2.40, J3.1, J3.2, J3.5, J3.6, J3.61, J3.62, J4.1, J4.2, J4.47, J4.48, R1.2, R2.2, R3.2, U1.7 (GND), U2.7 (GND), U3.7 (GND), U4.7 (GND), U5.7 (GND), U6.7 (GND), U7.7 (GND), U8.7 (GND), U9.7 (GND), U10.7 (GND)
unnamed: J3.3, JP27.1 (A)
unnamed: J3.4, JP28.1 (A)
unnamed: J3.63, JP26.1 (A)
unnamed: J3.64, JP47.1 (A)
unnamed: J4.3, JP67.1 (A)
unnamed: J4.4, JP68.1 (A)
unnamed: J4.49, JP66.1 (A)
unnamed: J4.50, JP69.1 (A)
unnamed: R1.1, U1.2
unnamed: R2.1, U1.5
unnamed: R3.1, U1.9
unnamed: R4.2, U5.10, U5.13
unnamed: R5.2, U10.10, U10.13

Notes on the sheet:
SCSI->FPGA (bus snoop)
QMTech FPGA Board
Hold the snoop bus deselected unless enabled by the FPGA
HD50 SCSI Connector TE Amplite .050 5787082-5
Ensure all other control lines remain high impedance until needed
Spare Gates. Held disabled.
Allow optional powering from TERMPWR supply
QMTech Zynq Bajie Snoop only
FPGA->SCSI Buffers
Ensure OpenDrain Control lines stay Disabled until needed
2x25 Pin Header Male Right angle

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
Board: 2 copper layers, 143 parts (0 on the bottom side), 184 nets, no tracks yet.
